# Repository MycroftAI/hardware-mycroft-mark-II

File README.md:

# Mycroft Mark II Hardware

*⛵️ Note that this repository is a work-in-progress. It will be updated and improved on over time.*

This repository contains all of the designs and technical details of the Mycroft Mark II Prototypes.

Each sub-directory represents a prototype device. Currently this consists of:
- [Mark II RPi OTS](./mark-II-rpi-ots) - the first Mark II prototype released in February 2020 made from off-the-shelf components. [Deprecated]
- [Mark II RPi DevKit](./mark-II-Rpi-devkit) - the second iteration of the Mark II prototype. This includes a custom daughterboard (SJ201) that integrates the components from the OTS prototype into a single PCB.

## Our open hardware principles
* **Copy our designs** – build your own Mycroft Mark 2 - Raspberry Pi Edition or its individual parts
* **Modify our designs** – remixing is encouraged
* **Sell products based on our designs** – commercial use is permitted
* **Always keep the open license** – contribute your output back to the community
* **Credit the original author(s)** – like they do in science

## Feedback or ideas

We are always keen to hear from the community about ways to improve these designs. Whether you're a hacker, maker, engineer, or something else - join us in the:
- [Community Forums](https://community.mycroft.ai)
- [Community Chat](https://chat.mycroft.ai)
- or email us at [dev@mycroft.ai](mailto:dev@mycroft.ai)

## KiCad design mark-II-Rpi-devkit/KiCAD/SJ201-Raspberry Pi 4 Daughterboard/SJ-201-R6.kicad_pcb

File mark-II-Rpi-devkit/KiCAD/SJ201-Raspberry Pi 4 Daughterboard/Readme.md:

**SJ201-Raspberry Pi 4 Daughterboard**

*⛵️ Note that this repository is a work-in-progress. It will be updated and improved on over time.*

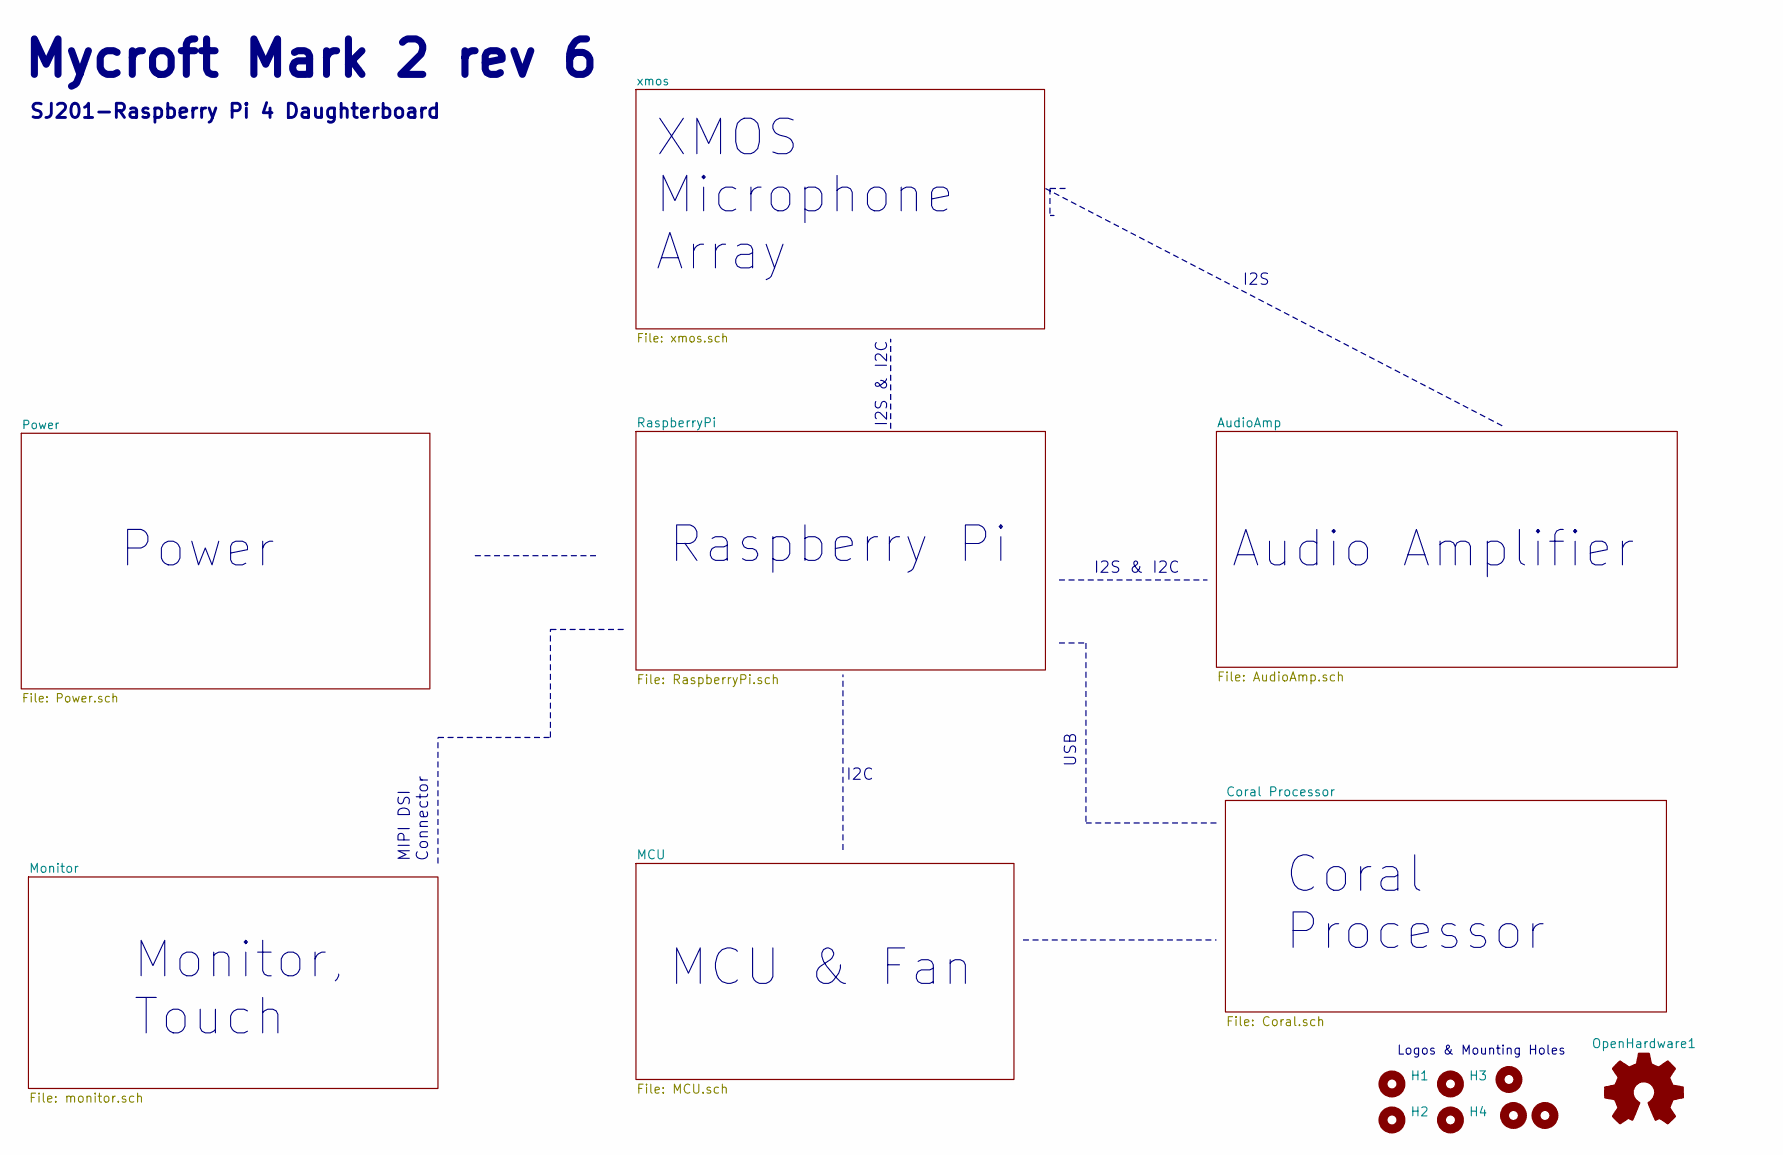
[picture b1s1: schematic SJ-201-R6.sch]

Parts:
H1, H2, H3, H4: MountingHole; MountingHole_3mm_Pad; MPN DNP
H5: MountingHole; mycroft_logo_graphic; MPN DNP
H6: MountingHole; simon-jester-logo; MPN DNP
H7: MountingHole; mycroft_logo_words; MPN DNP
OpenHardware1: Logo_Open_Hardware_Small; OSHW-Logo2_14.6x12mm_SilkScreen; MPN DNP

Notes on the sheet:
Raspberry Pi
Audio Amplifier
XMOS Microphone Array
Power
Monitor, Touch
Mycroft Mark 2 rev 6
MIPI DSI Connector
I2S
SJ201-Raspberry Pi 4 Daughterboard
USB
Coral Processor
Logos & Mounting Holes
I2S & I2C
MCU & Fan
I2C

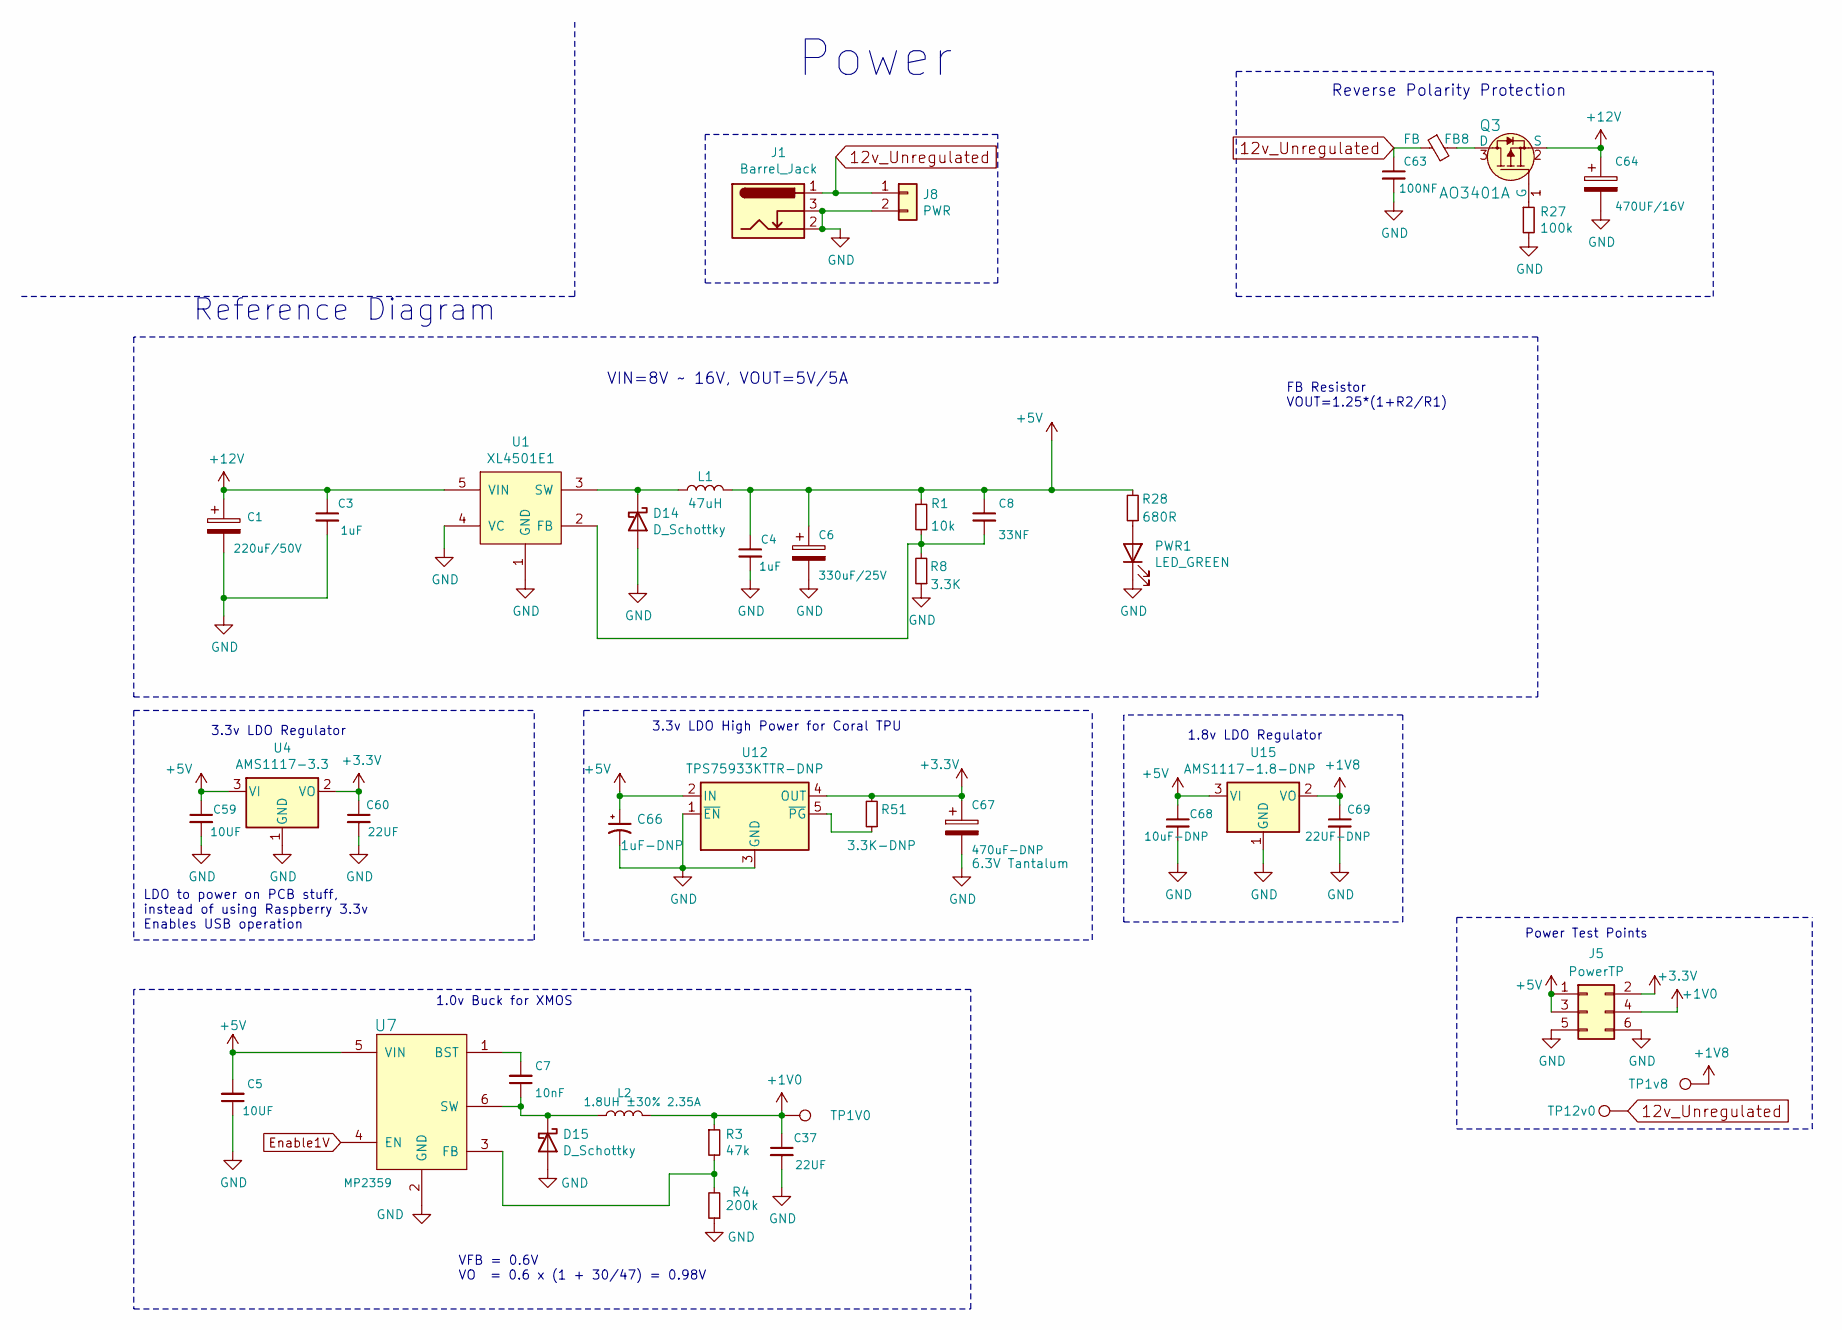
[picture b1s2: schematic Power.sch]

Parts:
C1: 220uF/50V; CP_Elec_10x10; MPN VE-221M1HTR-1010; LCSC C134732
C3, C4: 1uF; C_0402_1005Metric; MPN CL05A105KA5NQNC; LCSC C52923
C5, C59: 10UF; C_0402_1005Metric; MPN CC0402MRX5R5BB106; LCSC C15525
C6: 330uF/25V; CP_Elec_8x10.5; MPN RVT1E331M0810; LCSC C286135
C7: 10nF; C_0402_1005Metric; MPN CL05B103KB5NNNC; LCSC C15195
C8: 33NF; C_0402_1005Metric; MPN GRM155R71A333KA01D; LCSC C1585
C37, C60: 22UF; C_0603_1608Metric; MPN CL10A226MQ8NRNE; LCSC C59461
C63: 100NF; C_0402_1005Metric; MPN CC0402KRX7R8BB104; LCSC C1525
C64: 470UF/16V; CP_Elec_8x10.5; MPN SMD CAP Aluminum 470uF-16V;D8.0*H10.2mm; LCSC C176671
C66: 1uF-DNP; CP_EIA-3216-10_Kemet-I; MPN TAJA105K016RNJ-DNP; LCSC C7174-DNP
C67: 470uF-DNP; CP_EIA-7343-15_Kemet-W; MPN 6TPE470MAZU-DNP; LCSC C79114-DNP
C68: 10uF-DNP; C_0402_1005Metric; MPN CC0402MRX5R5BB106-DNP; LCSC C15525-DNP
C69: 22UF-DNP; C_0603_1608Metric; MPN CL10A226MQ8NRNE-DNP; LCSC C59461-DNP
D14: D_Schottky; D_SMA; MPN SS54F; LCSC C22452
D15: D_Schottky; D_SOD-123; MPN B5819W; LCSC C8598
FB8: FB; R_1206_3216Metric; MPN MLB3216-301P3A(f); LCSC C29107
J1: Barrel_Jack; BarrelJack_Horizontal; MPN DC-005-5A-2.0; LCSC C381116
J5: PowerTP; PinHeader_1x06_P1.27mm_Vertical_SMD_Pin1Left; MPN DNP; LCSC DNP
J8: PWR; PinHeader_1x02_P2.54mm_Vertical; MPN DNP
L1: 47uH; L_Wuerth_HCI-1365; MPN YSPI1365-470M; LCSC C497913
L2: 1.8UH ±30% 2.35A; L_Bourns-SRN4018; MPN SRR4018-1R8Y
PWR1: LED_GREEN; LED_0603_1608Metric; MPN 19-217/GHC-YR1S2/3T; LCSC C72043
Q3: AO3401A; SOT-23; MPN AO3401A; LCSC C306862
R1: 10k; R_0402_1005Metric; MPN RC0402FR-0710KL; LCSC C25744
R3: 47k; R_0402_1005Metric; MPN 0402WGF4702TCE; LCSC C25792
R4: 200k; R_0402_1005Metric; MPN 0402WGF2003TCE; LCSC C25764
R8: 3.3K; R_0402_1005Metric; MPN 0402WGF3301TCE; LCSC C25890
R27: 100k; R_0402_1005Metric; MPN RC0402JR-07100KL; LCSC C25741
R28: 680R; R_0402_1005Metric; MPN 0402WGF6800TCE; LCSC C25130
R51: 3.3K-DNP; R_0402_1005Metric; MPN 0402WGF3301TCE-DNP; LCSC C25890-DNP
TP1V0, TP1v8, TP12v0: TestPoint; TestPoint_Pad_D2.0mm; MPN DNP
U1: XL4501E1; TO-263-5_TabPin3; MPN XL4501E1; LCSC C73025
U4: AMS1117-3.3; SOT-223-3_TabPin2; MPN AMS1117-3.3; LCSC C6186
U7: MP2359; TSOT-23-6; MPN MP2359DJ-LF-Z; LCSC C14259
U12: TPS75933KTTR-DNP; TO-263-5_TabPin3; MPN TPS75933KTTR-DNP
U15: AMS1117-1.8-DNP; SOT-223-3_TabPin2; MPN AMS1117-1.8-DNP; LCSC C6185-DNP

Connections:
12v_Unregulated: C63.1, FB8.1, J1.1, J8.1, TP12v0.1
+1V0: C37.1, J5.4, L2.2, R3.1, TP1V0.1; also elsewhere on the board
+1V8: C69.1, TP1v8.1, U15.2 (VO); also elsewhere on the board
+5V: C4.1, C5.2, C6.1, C8.1, C59.1, C66.1, C68.1, J5.1, J5.3, L1.2, R1.1, R28.2, U4.3 (VI), U7.5 (VIN), U12.2 (IN), U15.3 (VI); also elsewhere on the board
Enable1V: U7.4 (EN); also elsewhere on the board
GND: C1.2, C3.2, C4.2, C5.1, C6.2, C37.2, C59.2, C60.2, C63.2, C64.2, C66.2, C67.2, C68.2, C69.2, D14.2 (A), D15.2 (A), J1.2, J1.3, J5.5, J5.6, J8.2, PWR1.1 (K), R4.1, R8.1, R27.2, U1.1 (GND), U1.4 (VC), U4.1 (GND), U7.2 (GND), U12.1 (~EN), U12.3 (GND), U15.1 (GND); also elsewhere on the board
unnamed: C7.1, D15.1 (K), L2.1, U7.6 (SW)
unnamed: C7.2, U7.1 (BST)
unnamed: C8.2, R1.2, R8.2, U1.2 (FB)
unnamed: D14.1 (K), L1.1, U1.3 (SW)
unnamed: FB8.2, Q3.3 (D)
unnamed: PWR1.2 (A), R28.1
unnamed: Q3.1 (G), R27.1
unnamed: R3.2, R4.2, U7.3 (FB)
unnamed: R51.1, U12.5 (~PG)
PVDD: C1.1, C3.1, C64.1, Q3.2 (S), U1.5 (VIN); also elsewhere on the board

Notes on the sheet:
Power
Reference Diagram
Reverse Polarity Protection
VIN=8V ~~ 16V, VOUT=5V/5A
FB Resistor VOUT=1.25*(1+R2/R1)
3.3v LDO Regulator
LDO to power on PCB stuff, instead of using Raspberry 3.3v Enables USB operation
VFB = 0.6V VO = 0.6 x (1 + 30/47) = 0.98V
1.0v Buck for XMOS
Power Test Points
3.3v LDO High Power for Coral TPU
1.8v LDO Regulator

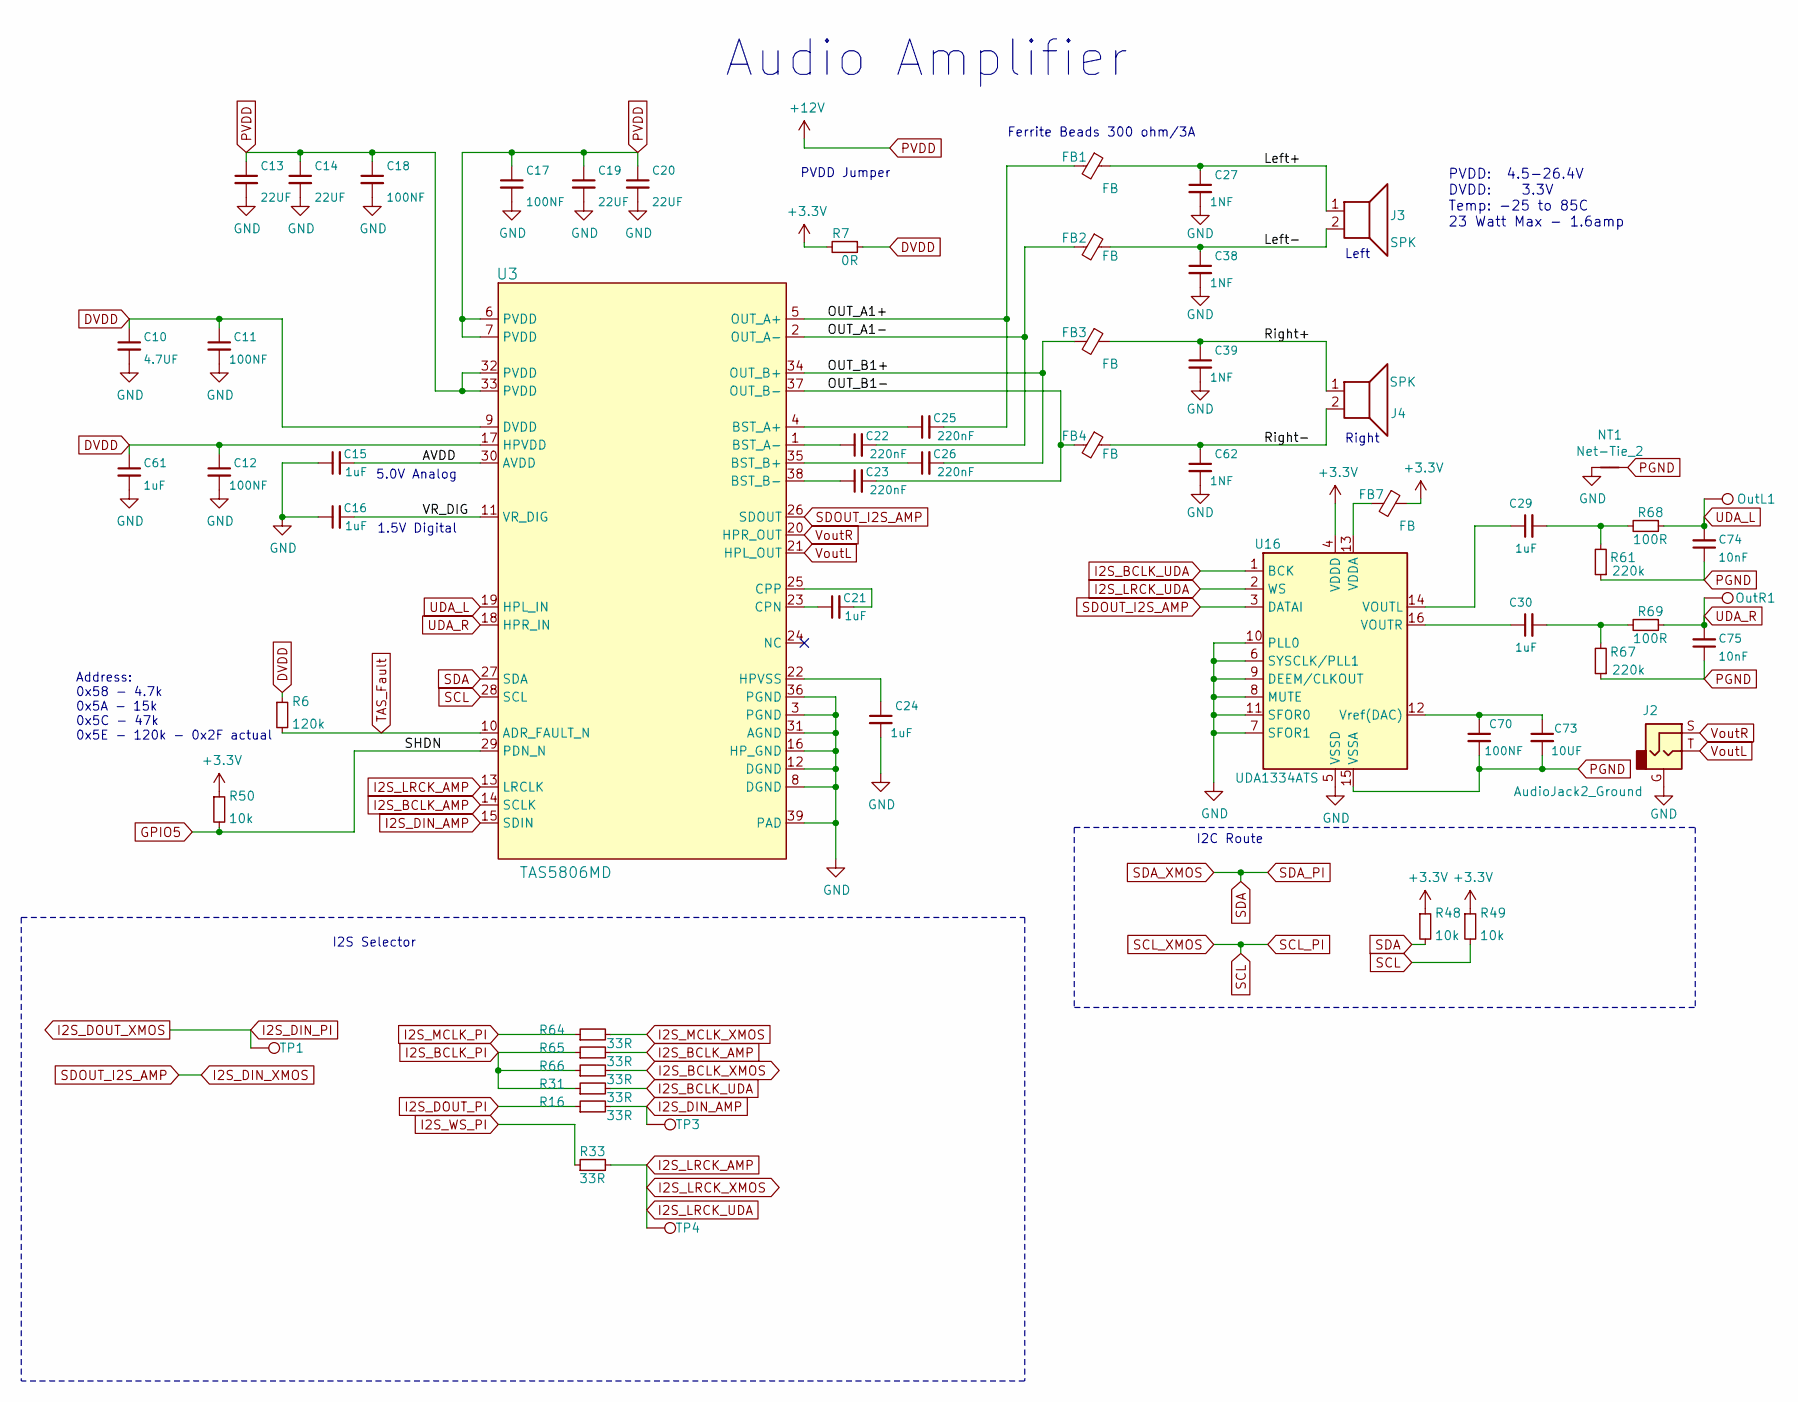
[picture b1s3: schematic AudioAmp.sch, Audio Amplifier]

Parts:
C10: 4.7UF; C_0402_1005Metric; MPN CL05A475MP5NRNC; LCSC C23733
C11, C12, C70: 100NF; C_0402_1005Metric; MPN CC0402KRX7R8BB104; LCSC C1525
C13, C14, C19, C20: 22UF; C_0603_1608Metric; MPN CL10A226MQ8NRNC; LCSC C59461
C15, C16, C21, C24, C29, C30, C61: 1uF; C_0402_1005Metric; MPN CL05A105KA5NQNC; LCSC C52923
C17, C18: 100NF; C_0603_1608Metric; MPN CC0603KRX7R9BB104; LCSC C14663
C22, C23, C25, C26: 220nF; C_0603_1608Metric; MPN CL10B224KA8NNNC; LCSC C21120
C27, C38, C39, C62: 1NF; C_0402_1005Metric; MPN 0402B102K500NT; LCSC C1523
C73: 10UF; C_0402_1005Metric; MPN CC0402MRX5R5BB106; LCSC C15525
C74, C75: 10nF; C_0402_1005Metric; MPN CL05B103KB5NNNC; LCSC C15195
FB1, FB2, FB3, FB4, FB7: FB; R_1206_3216Metric; MPN MLB3216-301P3A(f); LCSC C29107
J2: AudioJack2_Ground; Jack_3.5mm_PJ-3210; MPN PJ-3210-4A; LCSC C136686
J3, J4: SPK; JST_PH_B2B-PH-K_1x02_P2.00mm_Vertical; MPN B2B-PH-K-S(LF)(SN); LCSC C131337
NT1: Net-Tie_2; NetTie-2_SMD_Pad0.5mm; MPN DNP
OutL1: TestPoint; TestPoint_Pad_D2.0mm; MPN DNP
OutR1: TestPoint; TestPoint_Pad_D2.0mm; MPN DNP
R6: 120k; R_0402_1005Metric; MPN 0402WGF1203TCE; LCSC C25750
R7: 0R; R_0603_1608Metric; MPN 0603WAF0000T5E; LCSC C21189
R16, R31, R33, R64, R65, R66: 33R; R_0402_1005Metric; MPN 0402WGF330JTCE; LCSC C25105
R48, R49, R50: 10k; R_0402_1005Metric; MPN RC0402FR-0710KL; LCSC C25744
R61, R67: 220k; R_0402_1005Metric; MPN 0402WGF2203TCE; LCSC C25767
R68, R69: 100R; R_0402_1005Metric; MPN 0402WGF1000TCE; LCSC C25076
TP1, TP3, TP4: TestPoint; TestPoint_Pad_D2.0mm; MPN DNP
U3: TAS5806MD; TAS5806MDDCPR; MPN TAS5806MDDCPR
U16: UDA1334ATS; SSOP-16_4.4x5.2mm_P0.65mm; MPN UDA1334ATS/N2,118; LCSC C494494

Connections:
/AudioAmp/AVDD: C15.2, U3.30 (AVDD)
/AudioAmp/Left+: C27.1, FB1.1, J3.1
/AudioAmp/Left-: C38.1, FB2.1, J3.2
/AudioAmp/OUT_A1+: C25.2, FB1.2, U3.5 (OUT_A+)
/AudioAmp/OUT_A1-: C22.2, FB2.2, U3.2 (OUT_A-)
/AudioAmp/OUT_B1+: C26.2, FB3.2, U3.34 (OUT_B+)
/AudioAmp/OUT_B1-: C23.2, FB4.2, U3.37 (OUT_B-)
/AudioAmp/Right+: C39.1, FB3.1, J4.1
/AudioAmp/Right-: C62.1, FB4.1, J4.2
/AudioAmp/VR_DIG: C16.2, U3.11 (VR_DIG)
DVDD: C10.1, C11.1, C12.1, C61.1, R6.1, R7.1, U3.9 (DVDD), U3.17 (HPVDD)
GND: C10.2, C11.2, C12.2, C13.2, C14.2, C15.1, C16.1, C17.2, C18.2, C19.2, C20.2, C24.2, C27.2, C38.2, C39.2, C61.2, C62.2, J2.G, NT1.1, U3.3 (PGND), U3.8 (DGND), U3.12 (DGND), U3.16 (HP_GND), U3.31 (AGND), U3.36 (PGND), U3.39 (PAD), U16.5 (VSSD), U16.6 (SYSCLK/PLL1), U16.7 (SFOR1), U16.8 (MUTE), U16.9 (DEEM/CLKOUT), U16.10 (PLL0), U16.11 (SFOR0); also elsewhere on the board
GPIO5: R50.2, U3.29 (PDN_N); also elsewhere on the board
I2S_BCLK_AMP: R65.2, U3.14 (SCLK)
I2S_BCLK_PI: R31.1, R65.1, R66.1; also elsewhere on the board
I2S_BCLK_UDA: R31.2, U16.1 (BCK)
I2S_BCLK_XMOS: R66.2; also elsewhere on the board
I2S_DIN_AMP: R16.2, TP3.1, U3.15 (SDIN)
I2S_DIN_PI: TP1.1; also elsewhere on the board
I2S_DIN_XMOS: U3.26 (SDOUT), U16.3 (DATAI); also elsewhere on the board
I2S_DOUT_PI: R16.1; also elsewhere on the board
I2S_LRCK_AMP: R33.2, TP4.1, U3.13 (LRCLK), U16.2 (WS); also elsewhere on the board
I2S_MCLK_PI: R64.1; also elsewhere on the board
I2S_MCLK_XMOS: R64.2; also elsewhere on the board
I2S_WS_PI: R33.1; also elsewhere on the board
unnamed: C21.1, U3.23 (CPN)
unnamed: C21.2, U3.25 (CPP)
unnamed: C22.1, U3.1 (BST_A-)
unnamed: C23.1, U3.38 (BST_B-)
unnamed: C24.1, U3.22 (HPVSS)
unnamed: C25.1, U3.4 (BST_A+)
unnamed: C26.1, U3.35 (BST_B+)
unnamed: C29.1, U16.14 (VOUTL)
unnamed: C29.2, R61.2, R68.2
unnamed: C30.1, U16.16 (VOUTR)
unnamed: C30.2, R67.2, R69.2
unnamed: C70.1, C73.1, U16.12 (Vref(DAC))
unnamed: FB7.2, U16.13 (VDDA)
PGND: C70.2, C73.2, C74.1, C75.1, NT1.2, R61.1, R67.1, U16.15 (VSSA)
PVDD: C13.1, C14.1, C17.1, C18.1, C19.1, C20.1, U3.6 (PVDD), U3.7 (PVDD), U3.32 (PVDD), U3.33 (PVDD); also elsewhere on the board
SCL: R49.2, U3.28 (SCL); also elsewhere on the board
SDA: R48.2, U3.27 (SDA); also elsewhere on the board
TAS_Fault: R6.2, U3.10 (ADR_FAULT_N); also elsewhere on the board
UDA_L: C74.2, OutL1.1, R68.1, U3.19 (HPL_IN)
UDA_R: C75.2, OutR1.1, R69.1, U3.18 (HPR_IN)
VoutL: J2.T, U3.21 (HPL_OUT)
VoutR: J2.S, U3.20 (HPR_OUT)

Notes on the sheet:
Audio Amplifier
PVDD: 4.5-26.4V DVDD: 3.3V Temp: -25 to 85C 23 Watt Max - 1.6amp
Ferrite Beads 300 ohm/3A
PVDD Jumper
I2C Route
Right
Left
Address: 0x58 - 4.7k 0x5A - 15k 0x5C - 47k 0x5E - 120k - 0x2F actual
1.5V Digital
5.0V Analog
I2S Selector

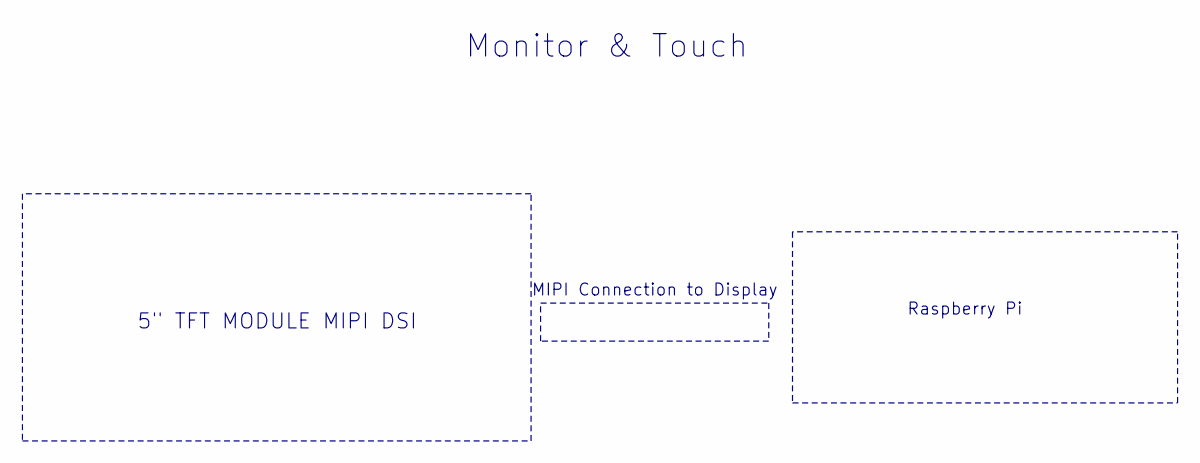
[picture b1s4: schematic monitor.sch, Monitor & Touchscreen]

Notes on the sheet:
Monitor & Touch
Raspberry Pi
MIPI Connection to Display
5" TFT MODULE MIPI DSI

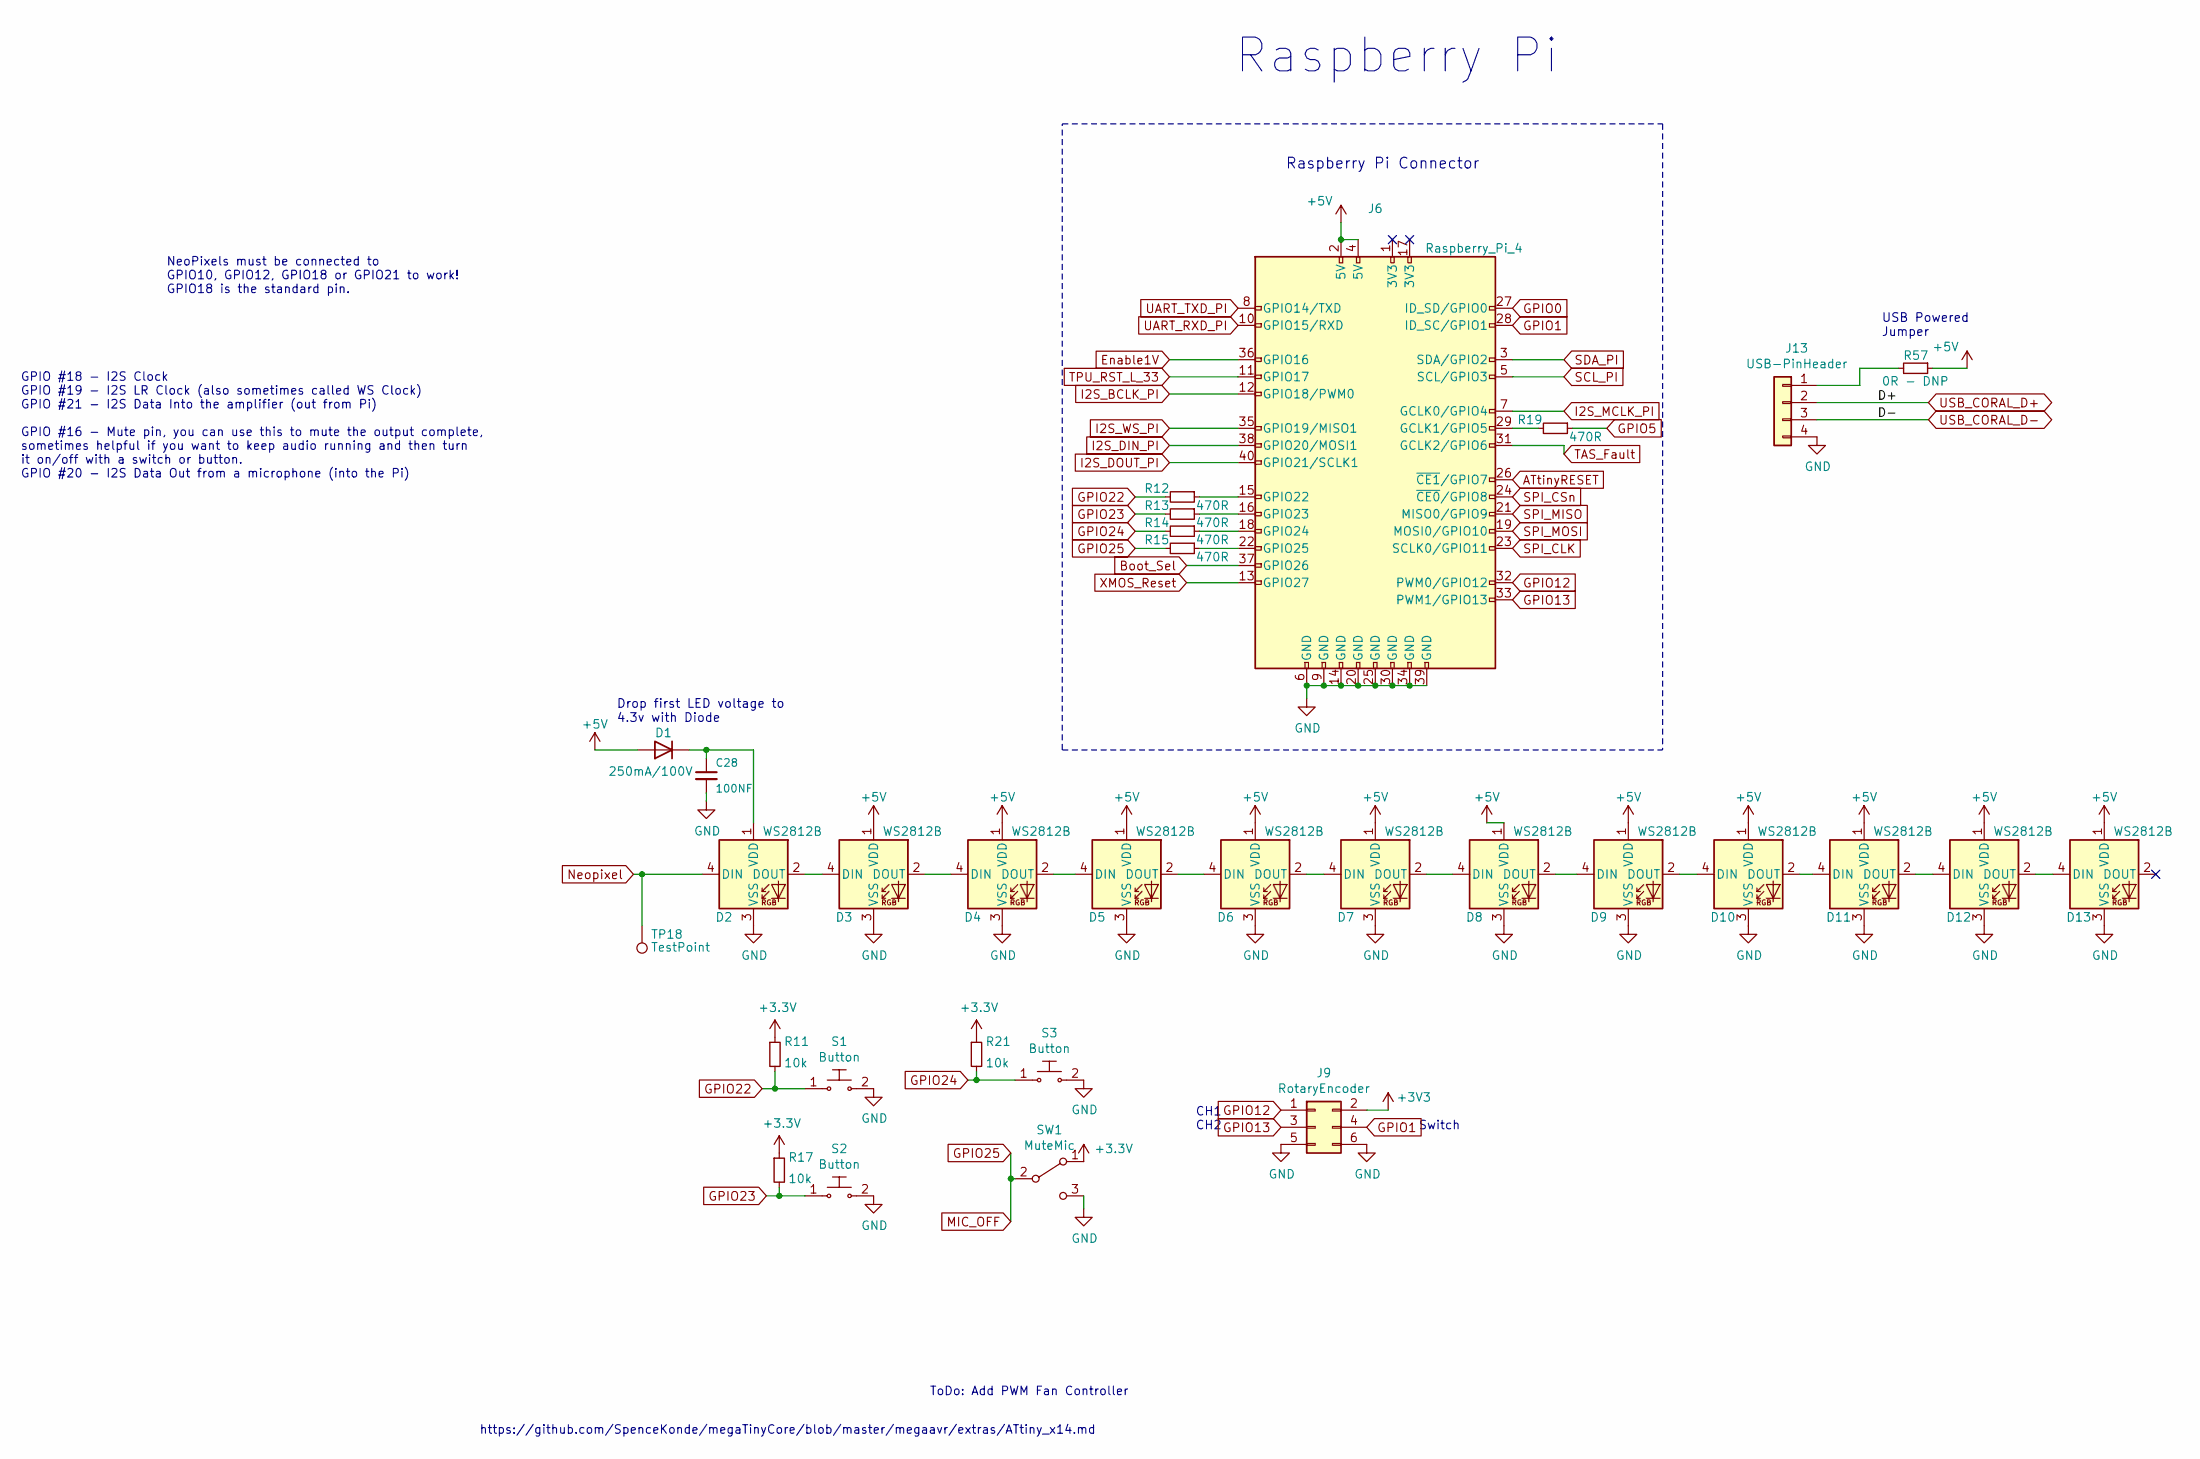
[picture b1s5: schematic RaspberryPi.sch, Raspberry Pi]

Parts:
C28: 100NF; C_0402_1005Metric; MPN CC0402KRX7R8BB104; LCSC C1525
D1: 250mA/100V; D_SOD-323F; MPN 1N4148WSF-7; LCSC C2128
D2: WS2812B; LED_WS2812_Mini_3.5x3.5mm_P1.1mm; MPN WS2812B-Mini; LCSC C527089
D3, D4, D5, D6, D7, D8, D9, D10, D11, D12, D13: WS2812B; LED_WS2812_Mini_3.5x3.5mm_P1.1mm; MPN WS2812B-MINI(WS2812B-3535); LCSC C527089
J6: Raspberry_Pi_4; PinSocket_2x20_P2.54mm_Horizontal; MPN FH412-2*20P 0.8U
J9: RotaryEncoder; PinHeader_2x03_P2.54mm_Vertical; MPN DNP
J13: USB-PinHeader; PinSocket_1x04_P2.54mm_Horizontal; MPN A2541HWR-4P; LCSC C225512
R11, R17, R21: 10k; R_0402_1005Metric; MPN RC0402FR-0710KL; LCSC C25744
R12, R13, R14, R19: 470R; R_0603_1608Metric; MPN 0603WAF4700T5E; LCSC C23179
R15: 470R; R_0603_1608Metric; MPN 0603WAF4700T5E
R57: 0R - DNP; R_0603_1608Metric; MPN DNP-0603WAF0000T5E; LCSC C21189-DNP
S1: Button; SW_SPST_TL3342; MPN TL3342F160QG/TR; Digikey EG2531TR-ND
S2, S3: Button; SW_SPST_TL3342; MPN TL3342F160QG/TR; Digi-Key_PN EG2531TR-ND
SW1: MuteMic; SW_SPDT_PCM12; MPN PCM12SMTR; Digikey 401-2016-2-ND
TP18: TestPoint; TestPoint_Pad_D2.0mm; MPN DNP

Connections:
+5V: D1.2 (A), D3.1 (VDD), D4.1 (VDD), D5.1 (VDD), D6.1 (VDD), D7.1 (VDD), D8.1 (VDD), D9.1 (VDD), D10.1 (VDD), D11.1 (VDD), D12.1 (VDD), D13.1 (VDD), J6.2 (5V), J6.4 (5V), R57.1; also elsewhere on the board
ATtinyRESET: J6.26 (~CE1~/GPIO7); also elsewhere on the board
Boot_Sel: J6.37 (GPIO26); also elsewhere on the board
Enable1V: J6.36 (GPIO16); also elsewhere on the board
GND: C28.2, D2.3 (VSS), D3.3 (VSS), D4.3 (VSS), D5.3 (VSS), D6.3 (VSS), D7.3 (VSS), D8.3 (VSS), D9.3 (VSS), D10.3 (VSS), D11.3 (VSS), D12.3 (VSS), D13.3 (VSS), J6.6 (GND), J6.9 (GND), J6.14 (GND), J6.20 (GND), J6.25 (GND), J6.30 (GND), J6.34 (GND), J6.39 (GND), J9.5, J9.6, J13.4, S1.2, S2.2, S3.2, SW1.3 (C); also elsewhere on the board
GPIO0: J6.27 (ID_SD/GPIO0); also elsewhere on the board
GPIO1: J6.28 (ID_SC/GPIO1), J9.4
GPIO5: R19.1; also elsewhere on the board
GPIO12: J6.32 (PWM0/GPIO12), J9.1
GPIO13: J6.33 (PWM1/GPIO13), J9.3
GPIO22: R11.2, R12.2, S1.1
GPIO23: R13.2, R17.2, S2.1
GPIO24: R14.2, R21.2, S3.1
GPIO25: R15.2, SW1.2 (B); also elsewhere on the board
I2S_BCLK_PI: J6.12 (GPIO18/PWM0); also elsewhere on the board
I2S_DIN_PI: J6.38 (GPIO20/MOSI1); also elsewhere on the board
I2S_DOUT_PI: J6.40 (GPIO21/SCLK1); also elsewhere on the board
I2S_MCLK_PI: J6.7 (GCLK0/GPIO4); also elsewhere on the board
I2S_WS_PI: J6.35 (GPIO19/MISO1); also elsewhere on the board
Neopixel: D2.4 (DIN), TP18.1; also elsewhere on the board
unnamed: C28.1, D1.1 (K), D2.1 (VDD)
unnamed: D2.2 (DOUT), D3.4 (DIN)
unnamed: D3.2 (DOUT), D4.4 (DIN)
unnamed: D4.2 (DOUT), D5.4 (DIN)
unnamed: D5.2 (DOUT), D6.4 (DIN)
unnamed: D6.2 (DOUT), D7.4 (DIN)
unnamed: D7.2 (DOUT), D8.4 (DIN)
unnamed: D8.2 (DOUT), D9.4 (DIN)
unnamed: D10.2 (DOUT), D11.4 (DIN)
unnamed: D9.2 (DOUT), D10.4 (DIN)
unnamed: D11.2 (DOUT), D12.4 (DIN)
unnamed: D12.2 (DOUT), D13.4 (DIN)
unnamed: J6.15 (GPIO22), R12.1
unnamed: J6.16 (GPIO23), R13.1
unnamed: J6.18 (GPIO24), R14.1
unnamed: J6.22 (GPIO25), R15.1
unnamed: J6.29 (GCLK1/GPIO5), R19.2
unnamed: J13.1, R57.2
SCL: J6.5 (SCL/GPIO3); also elsewhere on the board
SDA: J6.3 (SDA/GPIO2); also elsewhere on the board
SPI_CLK: J6.23 (SCLK0/GPIO11); also elsewhere on the board
SPI_CSn: J6.24 (~CE0~/GPIO8); also elsewhere on the board
SPI_MISO: J6.21 (MISO0/GPIO9); also elsewhere on the board
SPI_MOSI: J6.19 (MOSI0/GPIO10); also elsewhere on the board
TAS_Fault: J6.31 (GCLK2/GPIO6); also elsewhere on the board
TPU_RST_L_33: J6.11 (GPIO17); also elsewhere on the board
UART_RXD_PI: J6.10 (GPIO15/RXD); also elsewhere on the board
UART_TXD_PI: J6.8 (GPIO14/TXD); also elsewhere on the board
USB_CORAL_D+: J13.2; also elsewhere on the board
USB_CORAL_D-: J13.3; also elsewhere on the board
XMOS_Reset: J6.13 (GPIO27); also elsewhere on the board

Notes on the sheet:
Raspberry Pi Connector
Drop first LED voltage to 4.3v with Diode
ToDo: Add PWM Fan Controller
NeoPixels must be connected to GPIO10, GPIO12, GPIO18 or GPIO21 to work! GPIO18 is the standard pin.
GPIO #18 - I2S Clock GPIO #19 - I2S LR Clock (also sometimes called WS Clock) GPIO #21 - I2S Data Into the amplifier (out from Pi) GPIO #16 - Mute pin, you can use this to mute the output complete, sometimes helpful if you want to keep audio running and then turn it on/off with a switch or button. 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
https://github.com/SpenceKonde/megaTinyCore/blob/master/megaavr/extras/ATtiny_x14.md
Raspberry Pi
USB Powered Jumper
Switch
CH1 CH2

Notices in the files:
parts and their libraries:
Copyright 2016 Accelerated Designs. All rights reserved.
